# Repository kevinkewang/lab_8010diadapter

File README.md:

# lab_8010diadapter
I designed this DI box, which mounts directly onto the back of a Genelec 8010, for use during synthesizer development and workshops. It supports both line-level and Eurorack-level signals and includes a ground-lift function, helping to prevent damage to your speakers while you’re testing synthesizers. I have now made it open-source.

## Main features:
* The rotary switch offers four settings: Mute, -38dB (for Eurorack-level signals), -20dB, and Pass-through.
* When the rotary switch is set to "Mute," the indicator light can show the presence of a signal.
* The "Ground Lift" switch allows for the disconnection of the ground line, which can help eliminate noise in certain scenarios.
* A 10K:600 transformer is used for isolation, providing protection for your speakers.

## Schematics
**The component values in the PDF may be incorrect; please refer to the BOM table instead.**
https://github.com/kevinkewang/lab_8010diadapter/blob/main/hardware_design/circuit.pdf

## PCB

## Bill of materials
| Designator       | Qty | Value               | Description                     | Mouser Part No.                              |
|------------------|-----|---------------------|---------------------------------|----------------------------------------------|
| **PTH parts**    |     |                     |                                 |                                              |
| T1               | 1   | 10K:600             | audio transformer               |                                              |
| SW1              | 1   | ALPHA-SR1712F-0204  | rotary switch                   | 105-SR1712F-24NS                             |
| SW2              | 1   |                     | switch                          |                                              |
| J1               | 1   | 3.5mm Jack WQP518MA | Thonkiconn – 3.5mm Jack Sockets | https://www.thonk.co.uk/shop/thonkiconn/     |
| X1               | 1   | Neutrik XLR Jack    | Neutrik NC3MAAV                 | 568-NC3MAAV                                  |
| LED1             | 1   | Kingbright WP937EGW | RED/GREEN DIFFUSED 2-LEAD       | 604-WP937EGW                                 |
| C1               | 1   | 10uF ±10% 63V       | Film Capacitor                  | 871-B32522C106K                              |
| C2               | 1   | 10nF ±5% 50V        | Through-hole MLCC capacitor     | 594-K103J20C0GF5TH5                          |
| R1               | 1   | 620 Ohms            | 1/4W Through-Hole Resistor      | Resistor for LED                             |
| R4               | 1   | 51 Ohms             | 1/4W Through-Hole Resistor      | Resistor for Ground Lift                     |
| R5, R6           | 1   | 9.1kΩ               | 1/4W Through-Hole Resistor      | −38dB T-pad attenuation                      |
| R7               | 1   | 1kΩ                 | 1/4W Through-Hole Resistor      | −38dB T-pad attenuation                      |
| R8, R9           | 1   | 4.02kΩ              | 1/4W Through-Hole Resistor      | −20dB T-pad attenuation                      |
| R10              | 1   | 10kΩ                | 1/4W Through-Hole Resistor      | −20dB T-pad attenuation                      |
| **Mount parts**  |     |                     |                                 |                                              |
| nylon spacer     | 4   | M4 x 8mm x 1mm      |                                 |                                              |
| nylon spacer     | 4   | 4.2mm x 7mm x 5mm   |                                 |                                              |
| screw            | 4   | M4 x 16mm           |                                 |                                              |

## License
**The lab_8010diadapter project is made available under a CC-BY-NC-SA-3.0 license.**

If you want to make a few cases for your own use, go ahead and make them. If you're a synth studio and want to use them for product testing/demonstration etc, that's also welcome as long as it doesn't involve selling these directly. **Please do not make and sell these in bulk.**

## Links
Official website:  https://bitiworkshop.com/

Purchase here: https://store.bitiworkshop.com/

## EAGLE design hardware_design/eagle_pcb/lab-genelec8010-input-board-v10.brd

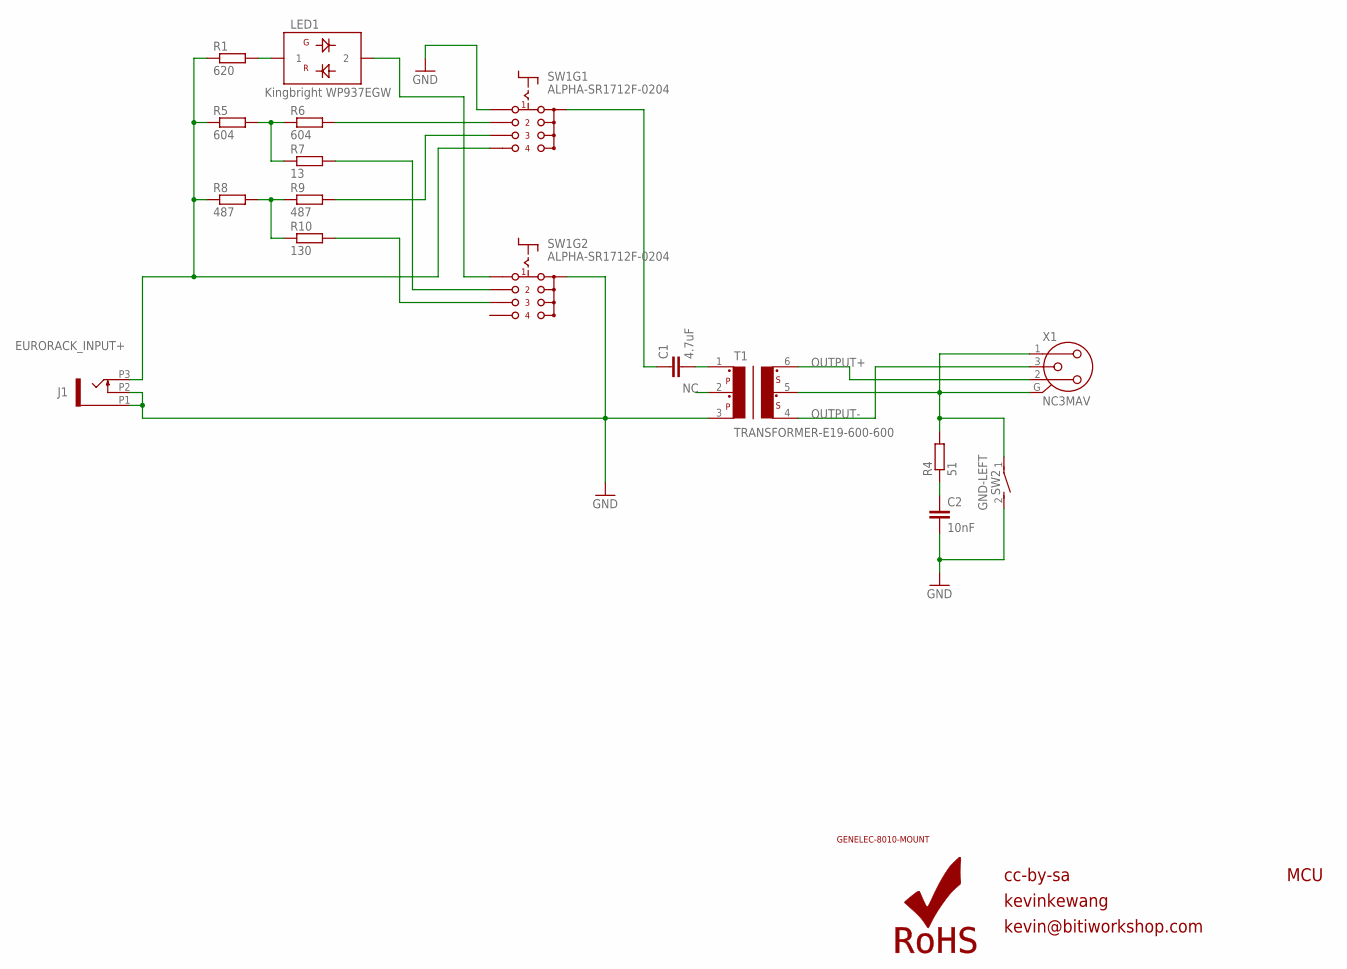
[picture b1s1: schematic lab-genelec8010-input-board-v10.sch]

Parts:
C1: 4.7uF; C15B5
C2: 10nF; C025-025X050
J1: OG-PJ301_PJ301_THONKICONN6; OG-PJ301_WQP_PJ_301M6
LED1: Kingbright WP937EGW; OG-LEDS_LED3MM
LOGO2: ROHS_LOGO; ROHS_LOGO_0.18_IN
R1: 620; 0204V
R4: 51; 0204V
R5, R6: 604; 0204V
R7: 13; 0204V
R8, R9: 487; 0204V
R10: 130; 0204V
SW1: ALPHA-SR1712F-0204
SW2: GND-LEFT; DS-01
T1: TRANSFORMER-E19-600-600
U$2: GENELEC-8010-MOUNT
X1: NC3MAV

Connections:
EURORACK_INPUT+: J1.P3 (3), R1.1, R5.1, R8.1, SW1.5 (4)
GND: C2.2, J1.P1 (1), J1.P2 (2), SW1.2 (1), SW1.COM10 (C), SW2.2, T1.3
unnamed: LED1.2, SW1.6 (1)
unnamed: LED1.1, R1.2
unnamed: C1.2, T1.1
unnamed: R5.2, R6.1, R7.1
unnamed: C2.1, R4.1
unnamed: R4.2, SW2.1, T1.5, X1.1, X1.G
unnamed: R6.2, SW1.3 (2)
unnamed: R7.2, SW1.7 (2)
unnamed: R8.2, R9.1, R10.1
unnamed: R9.2, SW1.4 (3)
unnamed: R10.2, SW1.8 (3)
unnamed: C1.1, SW1.COM1 (C)
NC: T1.2
OUTPUT+: T1.6, X1.2
OUTPUT-: T1.4, X1.3

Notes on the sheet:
cc-by-sa
MCU
kevinkewang
kevin@bitiworkshop.com

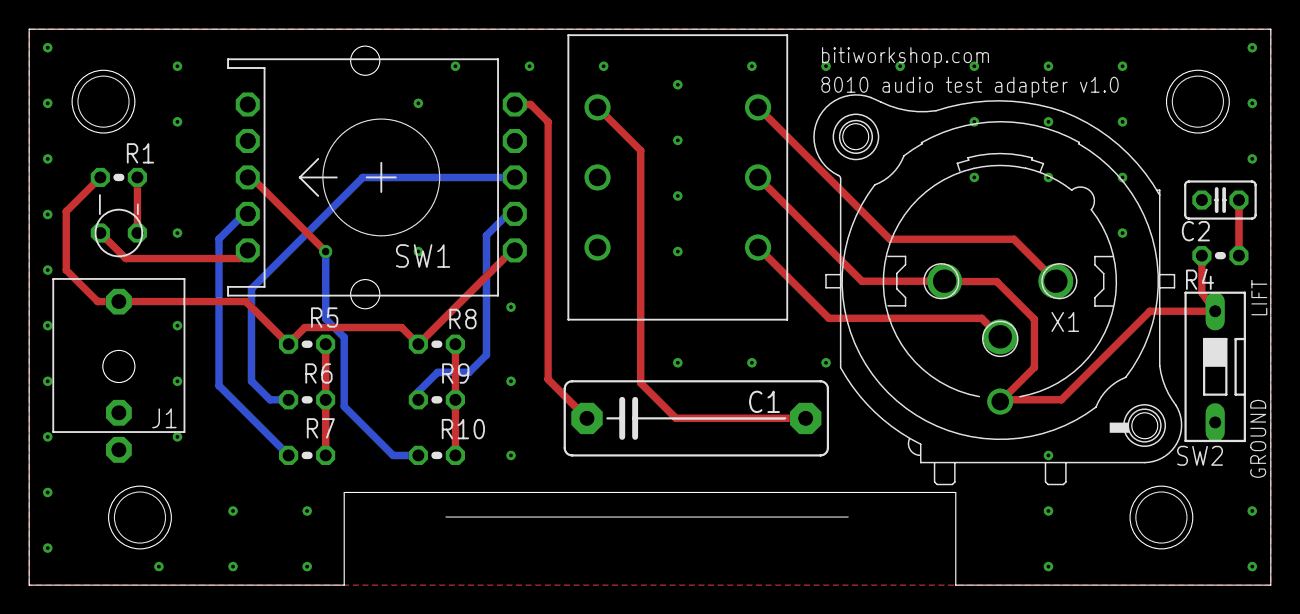
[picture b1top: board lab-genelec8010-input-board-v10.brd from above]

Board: 2 copper layers, 85.1 x 38.1 mm, 18 parts (1 on the bottom side), 16 nets.

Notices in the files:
parts and their libraries:
SparkFun-Aesthetics: Licensing: Creative Commons ShareAlike 4.0 International - https://creativecommons.org/licenses/by-sa/4.0
